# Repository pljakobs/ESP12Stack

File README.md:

# ESP12Stack
### An ESP12 Platform, adhering to the 30x30mm breakout boards often found but much more functional.
I have tested it with:
- ESPEasy
- SONOFF-TASMOTA
- Micropython
- Arduino
### Hardware
At this point, there is the base board which has:
- an ESP12 with all GPIO Pins brought to 2.54mm pin headers along the edge
- four WS2812B RGB or SK6812 RGBW individually addressable LEDs, which can be configured to be driven by various GPIO pins using 470Ohm resistors:
  - J02 -> GPIO2
  - J04 -> GPIO4
  - J05 -> GPIO5
  - J12 -> GPIO12
  - J13 -> GPIO13
only one of those should be installed at any given time
- low drop 3.3V regulator, the system can be powered either via the on-board USB connector or the 5V Vcc pin. Since there's no protection and those two 5V supplies form just one net, I suggest never to use both at the same time to avoid damage to your USB power source
- miniature switches for GPIO0 (FLASH) and RESET
- all necessary pull up / pull down resistors to be working as a stand alone device

In the FTDI vesion (currently untested) I have added an FTDI232 chip which should make the whole device in-place programmable, so no external USB-UART adapter is needed. Just plug it in to your PCs USB and you can talk to the ESP's UART
### There are a few other boards as well
- a 12-36V Switching Power Supply board that provides 5V (provided the feedback resistors are set correctly) to power the stack in an environment that requires those power levels (like a car)
- a five channel MOSFET board that can drive common anode LED strips
- an "experimentation" board that only has the VCC and GND pins pulled out to the outer row of mounting holes and otherwise offers as much of a "standard" layout board as possible for your own devices
### What I'm, working on:
the next board to come should be a display that just plugs on top of the base board, offering 240x240px through I2C

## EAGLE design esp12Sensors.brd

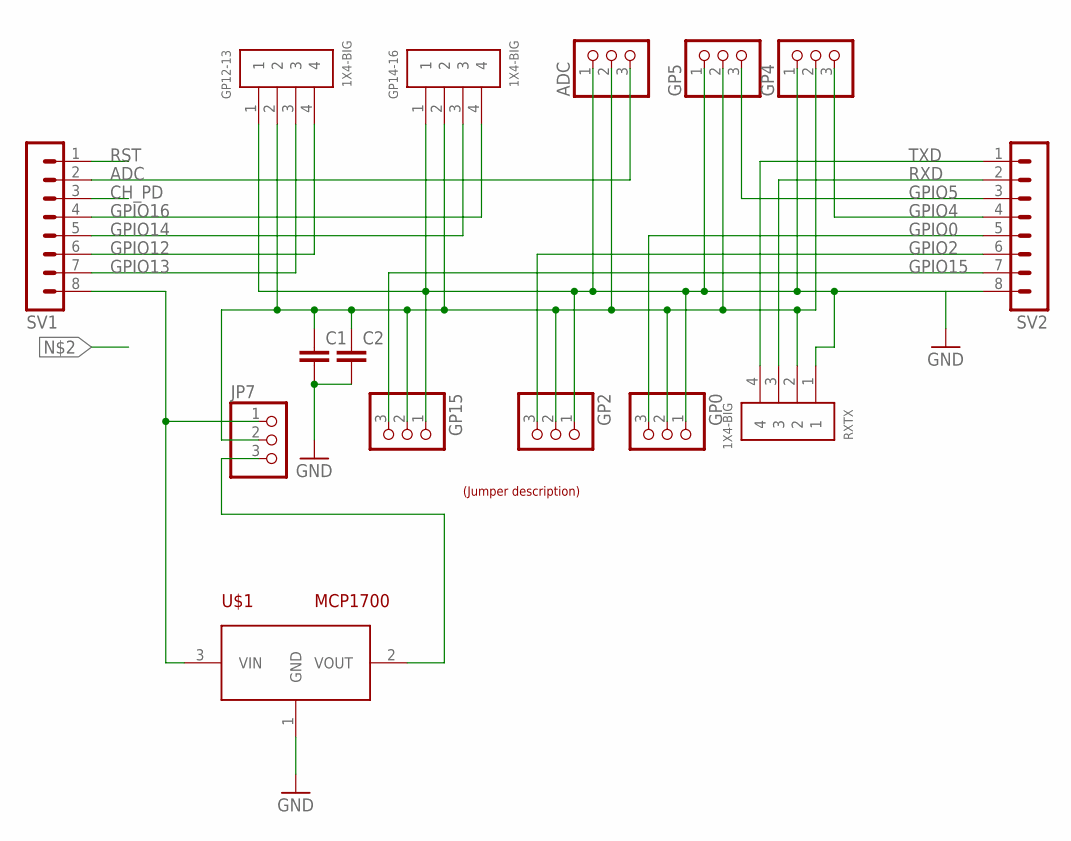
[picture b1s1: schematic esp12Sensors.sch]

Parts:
ADC: PINHD-1X3; 1X03
C1, C2: C-EUC0805; C0805
GP0, GP2, GP4, GP5, GP15: PINHD-1X3; 1X03
GP12-13, GP14-16: 1X4-BIG; 1X04-BIG
JP7: PINHD-1X3; 1X03
RXTX: 1X4-BIG; 1X04-BIG
SV1, SV2: MA08-1
U$1: MCP1700; SOT-23
U$2: LABEL_JUMPER_1X3; JUMP3_DESC

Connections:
3V3: JP7.3, U$1.2 (VOUT)
ADC: ADC.3, SV1.2
CH_PD: SV1.3
GND: ADC.1, C1.2, C2.2, GP0.1, GP2.1, GP4.1, GP5.1, GP12-13.1, GP14-16.1, GP15.1, RXTX.1, SV2.8, U$1.1 (GND)
GP12-13: JP7.1, SV1.8, U$1.3 (VIN)
GPIO0: GP0.3, SV2.5
GPIO2: GP2.3, SV2.6
GPIO4: GP4.3, SV2.4
GPIO5: GP5.3, SV2.3
GPIO12: GP12-13.3, SV1.7
GPIO13: GP12-13.4, SV1.6
GPIO14: GP14-16.3, SV1.5
GPIO15: GP15.3, SV2.7
GPIO16: GP14-16.4, SV1.4
RST: SV1.1
RXD: RXTX.3, SV2.2
TXD: RXTX.4, SV2.1
VCC: ADC.2, C1.1, C2.1, GP0.2, GP2.2, GP4.2, GP5.2, GP12-13.2, GP14-16.2, GP15.2, JP7.2, RXTX.2

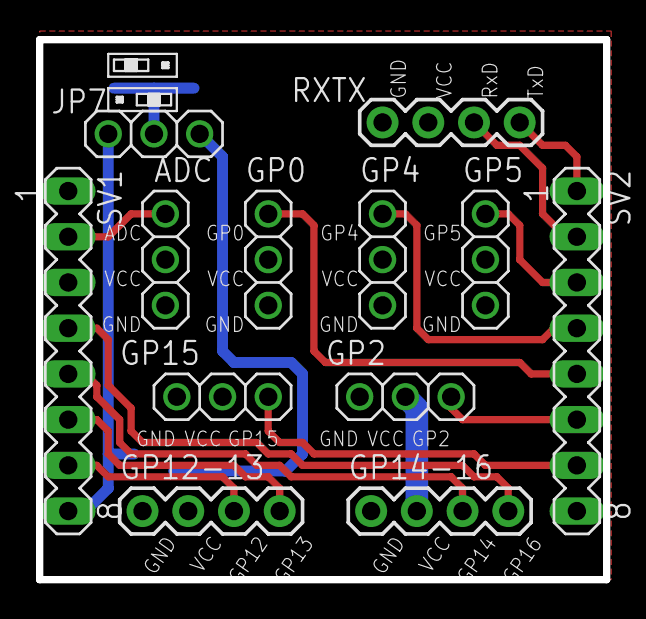
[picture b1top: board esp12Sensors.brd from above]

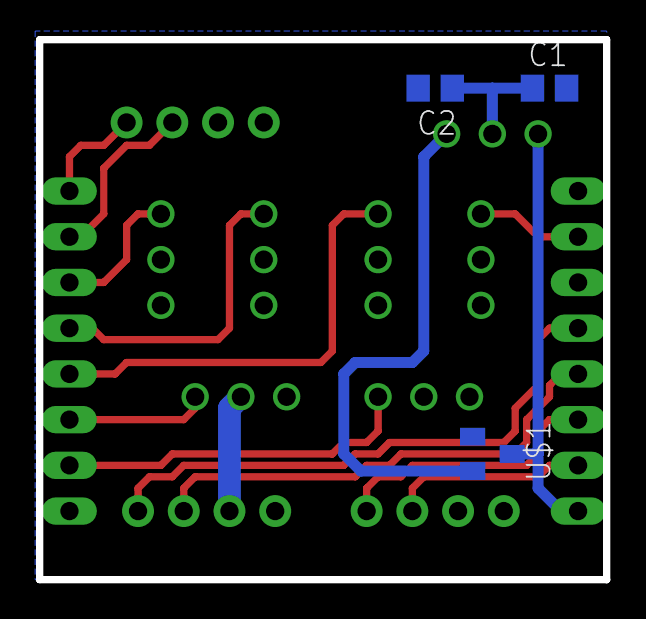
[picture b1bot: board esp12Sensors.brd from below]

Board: 2 copper layers, 31.5 x 30.0 mm, 16 parts (3 on the bottom side), 16 nets.

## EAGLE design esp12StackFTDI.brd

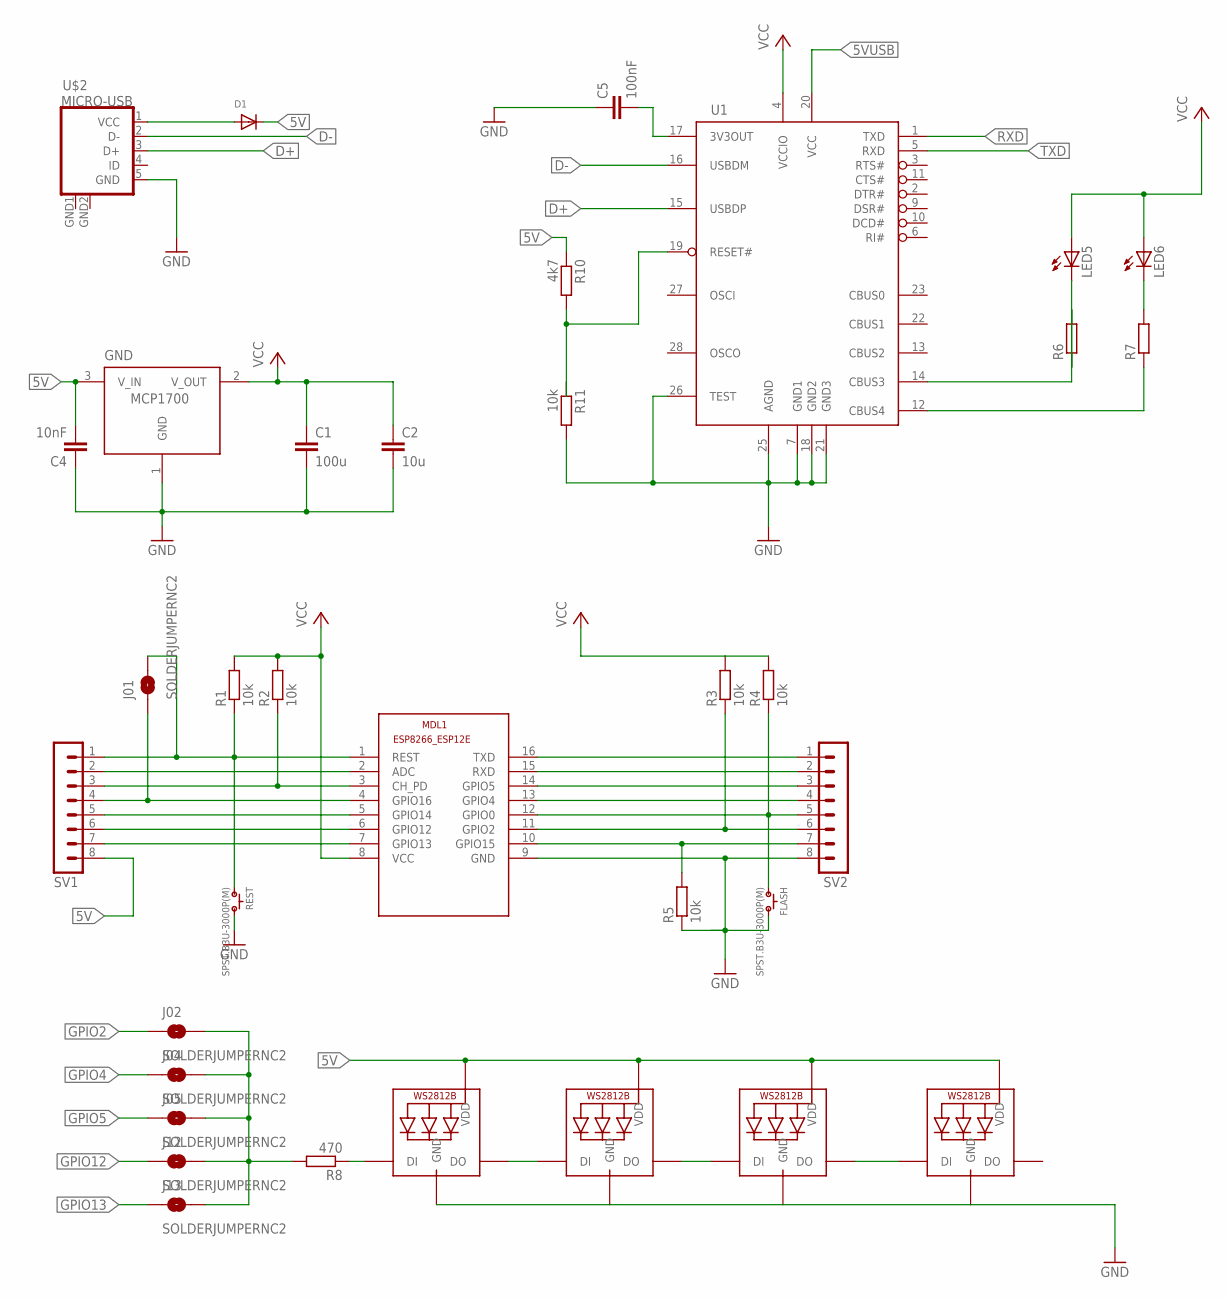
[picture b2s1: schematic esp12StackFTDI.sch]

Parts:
C1: 100u; C0805
C2: 10u; C0805
C4: 10nF; C0805
C5: 100nF; C0805
D1: DIODESOD-323F; SOD-323F
FLASH: SPST.B3U-3000P(M); B3U-3000P(M)
GND: MCP1700SOT23; SOT-23
J01, J02, J04, J05, J12, J13: SOLDERJUMPERNC2; SJ_2S-NOTRACE
LED1, LED2, LED3, LED4: WS2812B5050; WS2812B
LED5, LED6: LEDCHIPLED_0603; CHIPLED_0603
MDL1: ESP8266-12EESP8266-ESP12E; ESP8266-ESP12E
R1, R2, R3, R4, R5, R11: 10k; R0603
R6, R7: R-EU_R0603; R0603
R8: 470; R0603
R10: 4k7; R0603
REST: SPST.B3U-3000P(M); B3U-3000P(M)
SV1, SV2: MA08-1
U1: FT232RL; SSOP28DB
U$2: MICRO-USB

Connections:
3V3: C1.1, C2.1, GND.2 (V_OUT), LED5.A, LED6.A, MDL1.8 (VCC), R1.2, R2.2, R3.2, R4.2, U1.4 (VCCIO)
3V3OUT: C5.2, U1.17 (3V3OUT)
5V: C4.2, D1.C, GND.3 (V_IN), LED1.1-VDD (VDD), LED2.1-VDD (VDD), LED3.1-VDD (VDD), LED4.1-VDD (VDD), R10.1, SV1.8, U1.20 (VCC)
5VUSB: D1.A, U$2.1 (VCC)
ADC: MDL1.2 (ADC), SV1.2
CBUS3: R6.2, U1.14 (CBUS3)
CBUS4: R7.1, U1.12 (CBUS4)
CH_PD: MDL1.3 (CH_PD), R2.1, SV1.3
D+: U1.15 (USBDP), U$2.3 (D+)
D-: U1.16 (USBDM), U$2.2 (D-)
DIN1: J02.2, J04.2, J05.2, J12.2, J13.2, R8.2
DOUT1DIN2: LED1.2-DOUT (DO), LED2.4-DIN (DI)
DOUT2DIN3: LED2.2-DOUT (DO), LED3.4-DIN (DI)
DOUT3DIN4: LED3.2-DOUT (DO), LED4.4-DIN (DI)
GND: C1.2, C2.2, C4.1, C5.1, FLASH.2, GND.1 (GND), LED1.3-GND (GND), LED2.3-GND (GND), LED3.3-GND (GND), LED4.3-GND (GND), MDL1.9 (GND), R5.1, R11.2, REST.2, SV2.8, U1.7 (GND1), U1.18 (GND2), U1.21 (GND3), U1.25 (AGND), U1.26 (TEST), U$2.5 (GND), U$2.GND1 (GND), U$2.GND2 (GND)
GPIO0: FLASH.1, MDL1.12 (GPIO0), R4.1, SV2.5
GPIO2: J02.1, MDL1.11 (GPIO2), R3.1, SV2.6
GPIO4: J04.1, MDL1.13 (GPIO4), SV2.4
GPIO5: J05.1, MDL1.14 (GPIO5), SV2.3
GPIO12: J12.1, MDL1.6 (GPIO12), SV1.6
GPIO13: J13.1, MDL1.7 (GPIO13), SV1.7
GPIO14: MDL1.5 (GPIO14), SV1.5
GPIO15: MDL1.10 (GPIO15), R5.2, SV2.7
GPIO16: J01.1, MDL1.4 (GPIO16), SV1.4
LED_RX: LED6.C, R7.2
LED_TX: LED5.C, R6.1
unnamed: LED1.4-DIN (DI), R8.1
RESET: R10.2, R11.1, U1.19 (RESET#)
REST: J01.2, MDL1.1 (REST), R1.1, REST.1, SV1.1
RXD: MDL1.15 (RXD), SV2.2, U1.1 (TXD)
TXD: MDL1.16 (TXD), SV2.1, U1.5 (RXD)

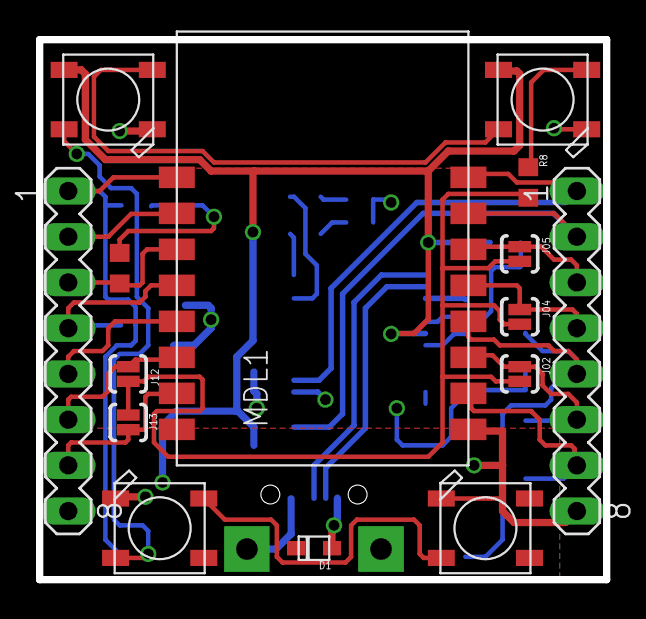
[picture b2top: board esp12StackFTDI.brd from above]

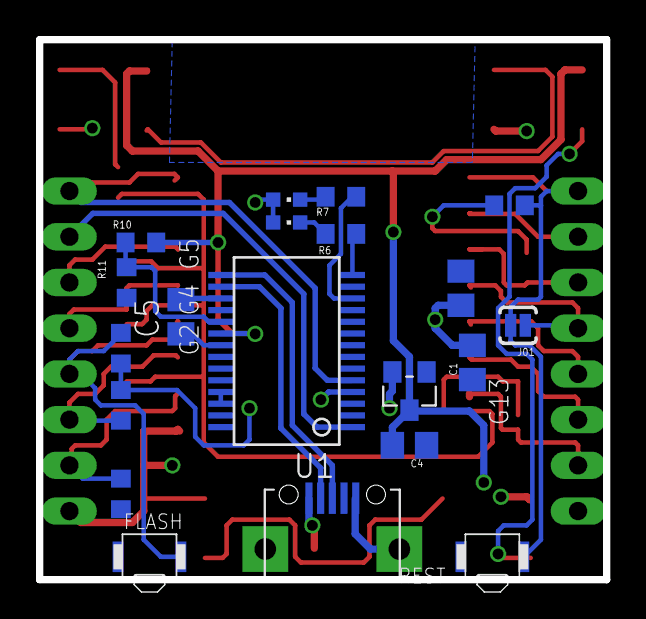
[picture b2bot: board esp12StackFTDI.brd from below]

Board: 2 copper layers, 31.5 x 30.0 mm, 35 parts (20 on the bottom side), 31 nets.

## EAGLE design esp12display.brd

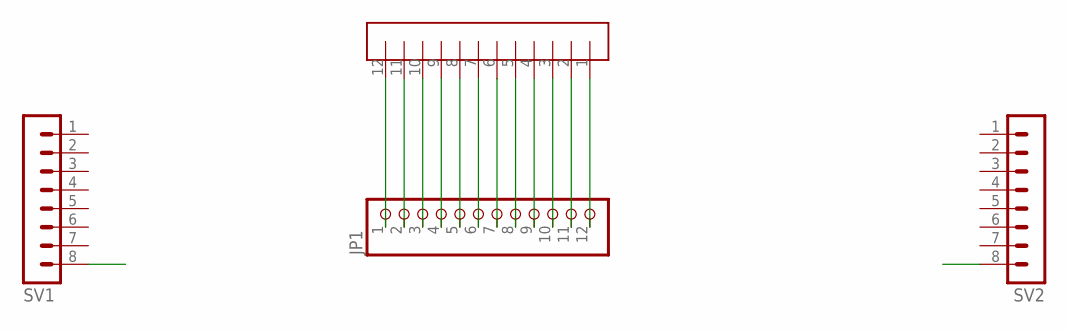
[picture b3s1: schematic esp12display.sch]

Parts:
JP1: PINHD-1X12; 1X12
SV1, SV2: MA08-1
U$1: 12PIN_LCD_PADS; PINS_ONLY

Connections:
GND: SV2.8
unnamed: JP1.1, U$1.12
unnamed: JP1.2, U$1.11
unnamed: JP1.3, U$1.10
unnamed: JP1.4, U$1.9
unnamed: JP1.5, U$1.8
unnamed: JP1.6, U$1.7
unnamed: JP1.7, U$1.6
unnamed: JP1.8, U$1.5
unnamed: JP1.9, U$1.4
unnamed: JP1.10, U$1.3
unnamed: JP1.11, U$1.2
unnamed: JP1.12, U$1.1

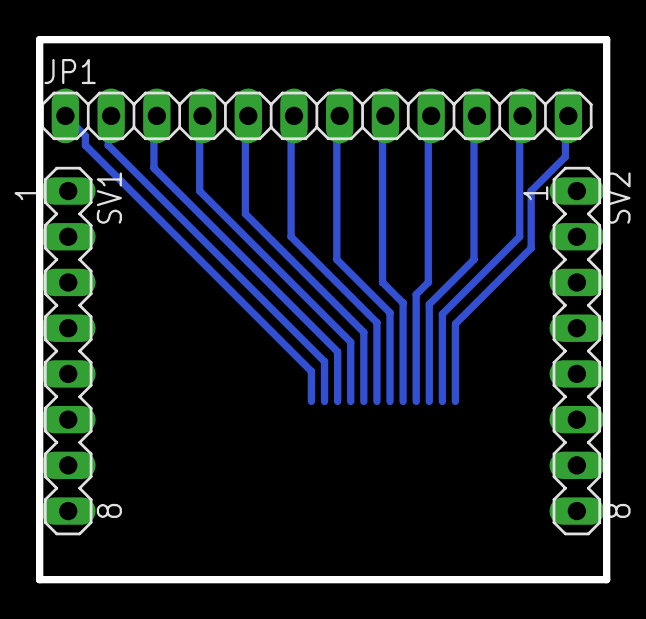
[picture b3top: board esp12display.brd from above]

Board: 2 copper layers, 31.5 x 30.0 mm, 4 parts (1 on the bottom side), 12 nets.

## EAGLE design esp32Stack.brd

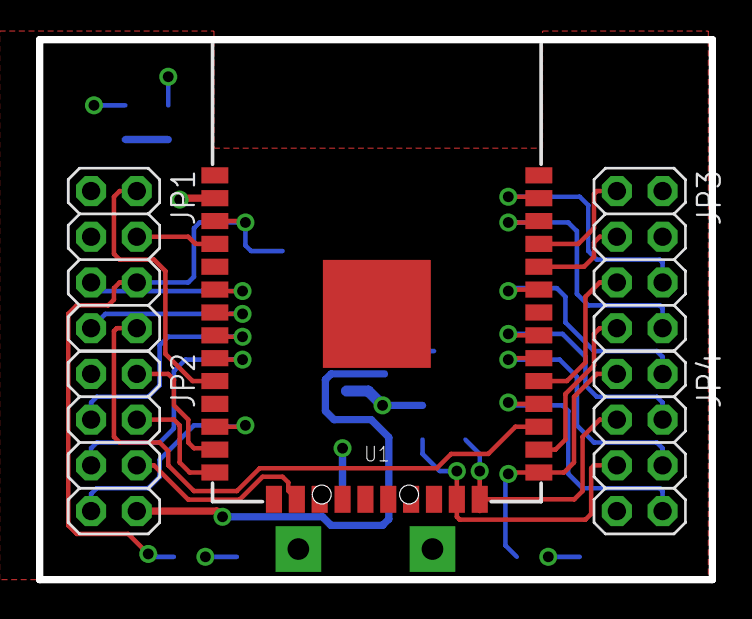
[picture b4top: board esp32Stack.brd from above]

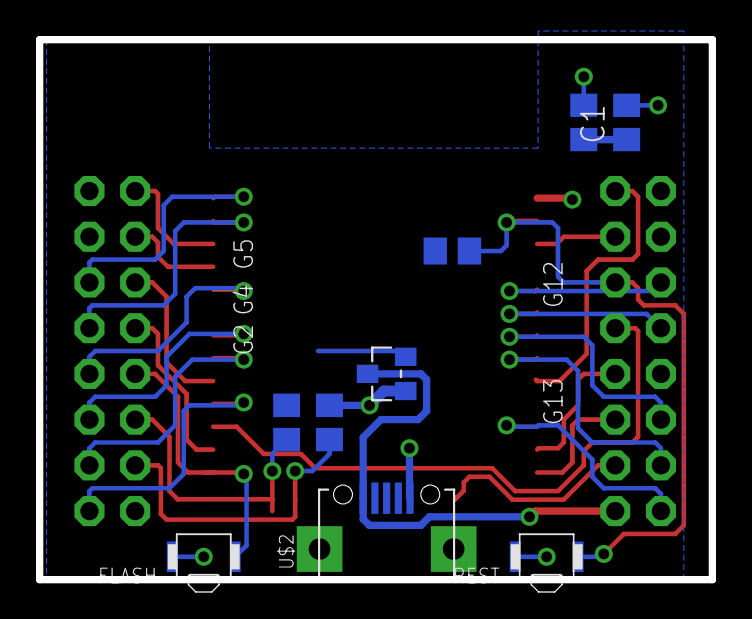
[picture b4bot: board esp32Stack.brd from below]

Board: 2 copper layers, 37.4 x 30.0 mm, 14 parts (9 on the bottom side), 28 nets.

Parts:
C1: 100u; C0805
C2: 10u; C0805
FLASH: SPST.B3U-3000P(M); B3U-3000P(M)
GND: MCP1700SOT23; SOT-23
JP1, JP2, JP3, JP4: 2X04
R2, R3, R5: 10k; R0805
REST: SPST.B3U-3000P(M); B3U-3000P(M)
U1: ESP-WROOM-03
U$2: MICRO-USB

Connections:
3V3: C1.1, C2.1, GND.2, R2.2, R3.2, U1.2
+5V: GND.3, JP2.8, U$2.1
ADC: JP1.4, U1.4
EN: JP1.6, R2.1, REST.1, U1.3
GND: C1.2, C2.2, FLASH.2, GND.1, JP4.7, R5.1, REST.2, U1.1, U1.5, U1.15, U1.38, U1.GND, U$2.5, U$2.GND1, U$2.GND2
GPIO0: FLASH.1, JP4.1, U1.25
GPIO2: JP4.3, R3.1, U1.24
GPIO4: JP3.7, U1.26
GPIO5: JP3.5, U1.29
GPIO12: JP2.4, U1.14
GPIO13: JP2.6, U1.16
GPIO14: JP2.2, U1.13
GPIO15: JP4.5, R5.2, U1.23
GPIO16: JP1.8, U1.27
GPIO17: JP4.8, U1.28
GPIO18: JP4.6, U1.30
GPIO19: JP4.4, U1.31
GPIO21: JP4.2, U1.33
GPIO22: JP3.8, U1.36
GPIO23: JP3.6, U1.37
GPIO25: JP1.2, U1.10
GPIO27: JP2.7, U1.12
GPIO32: JP2.3, U1.8
GPIO33: JP2.5, U1.9
GPIO34: JP1.5, U1.6
GPIO35: JP1.7, U1.7
RXD: JP3.3, U1.34
TXD: JP3.1, U1.35

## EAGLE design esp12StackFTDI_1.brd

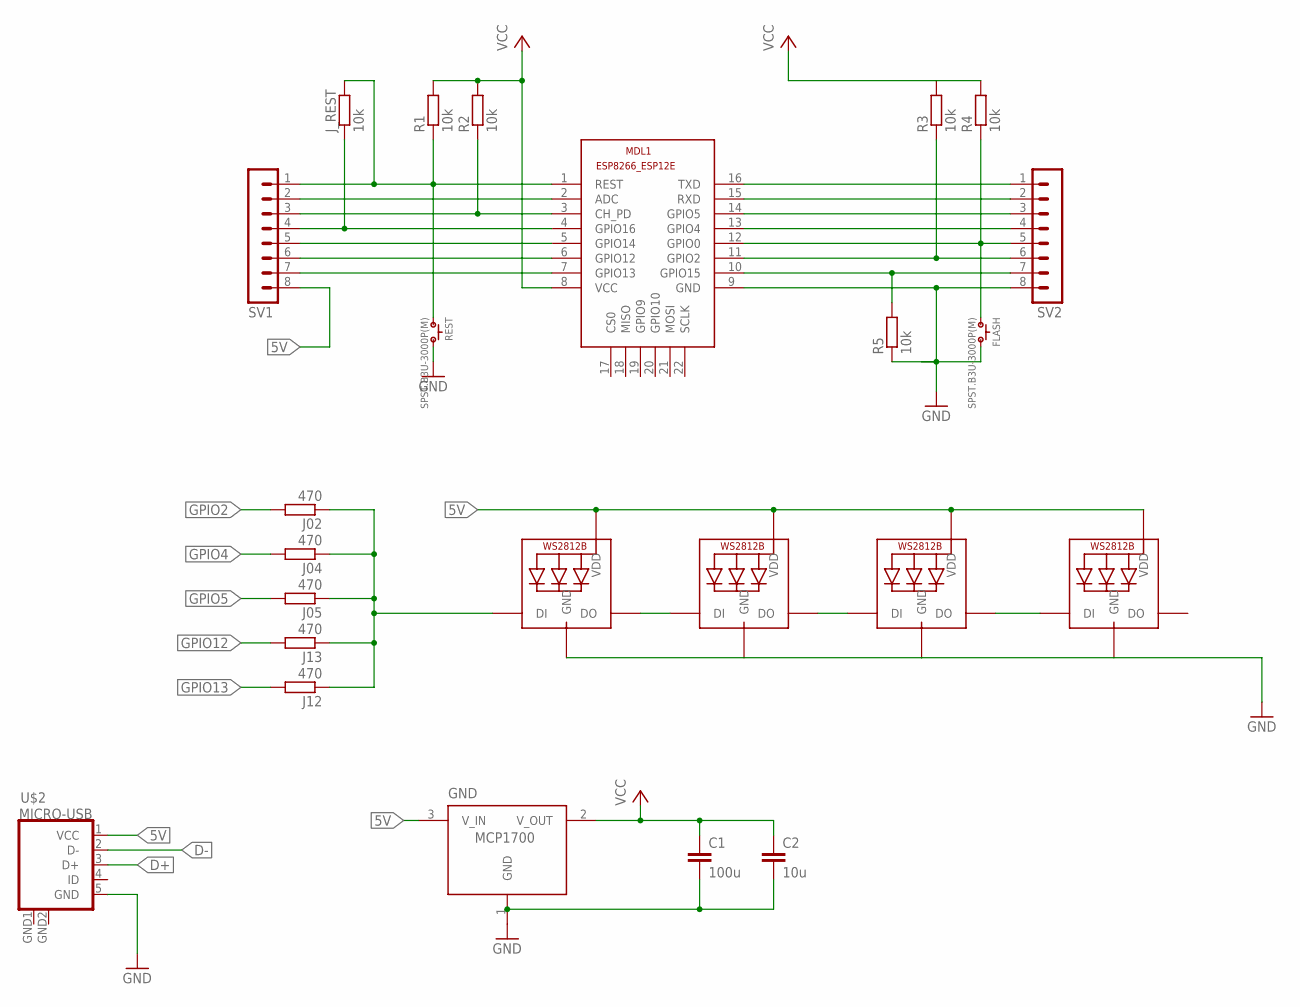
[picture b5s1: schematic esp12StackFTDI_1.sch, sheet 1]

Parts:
C1: 100u; C0805
C2: 10u; C0805
FLASH: SPST.B3U-3000P(M); B3U-3000P(M)
GND: MCP1700SOT23; SOT-23
J02, J04, J05, J12, J13: 470; R0603
J_REST: 10k; R0603
LED1, LED2, LED3, LED4: WS2812B5050; WS2812B
MDL1: ESP8266-12EESP8266-ESP12E; ESP8266-ESP12E
R1, R2, R3, R4, R5: 10k; R0603
REST: SPST.B3U-3000P(M); B3U-3000P(M)
SV1, SV2: MA08-1
U$2: MICRO-USB

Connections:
3V3: C1.1, C2.1, GND.2 (V_OUT), MDL1.8 (VCC), R1.2, R2.2, R3.2, R4.2; also elsewhere on the board
5V: GND.3 (V_IN), LED1.1-VDD (VDD), LED2.1-VDD (VDD), LED3.1-VDD (VDD), LED4.1-VDD (VDD), SV1.8, U$2.1 (VCC); also elsewhere on the board
ADC: MDL1.2 (ADC), SV1.2
CH_PD: MDL1.3 (CH_PD), R2.1, SV1.3
D+: U$2.3 (D+); also elsewhere on the board
D-: U$2.2 (D-); also elsewhere on the board
DIN1: J02.1, J04.1, J05.1, J12.1, J13.1, LED1.4-DIN (DI)
DOUT1DIN2: LED1.2-DOUT (DO), LED2.4-DIN (DI)
DOUT2DIN3: LED2.2-DOUT (DO), LED3.4-DIN (DI)
DOUT3DIN4: LED3.2-DOUT (DO), LED4.4-DIN (DI)
GND: C1.2, C2.2, FLASH.2, GND.1 (GND), LED1.3-GND (GND), LED2.3-GND (GND), LED3.3-GND (GND), LED4.3-GND (GND), MDL1.9 (GND), R5.1, REST.2, SV2.8, U$2.5 (GND), U$2.GND1 (GND), U$2.GND2 (GND); also elsewhere on the board
GPIO0: FLASH.1, MDL1.12 (GPIO0), R4.1, SV2.5
GPIO2: J02.2, MDL1.11 (GPIO2), R3.1, SV2.6
GPIO4: J04.2, MDL1.13 (GPIO4), SV2.4
GPIO5: J05.2, MDL1.14 (GPIO5), SV2.3
GPIO12: J13.2, MDL1.6 (GPIO12), SV1.6
GPIO13: J12.2, MDL1.7 (GPIO13), SV1.7
GPIO14: MDL1.5 (GPIO14), SV1.5
GPIO15: MDL1.10 (GPIO15), R5.2, SV2.7
GPIO16: J_REST.1, MDL1.4 (GPIO16), SV1.4
REST: J_REST.2, MDL1.1 (REST), R1.1, REST.1, SV1.1
RXD: MDL1.15 (RXD), SV2.2; also elsewhere on the board
TXD: MDL1.16 (TXD), SV2.1; also elsewhere on the board

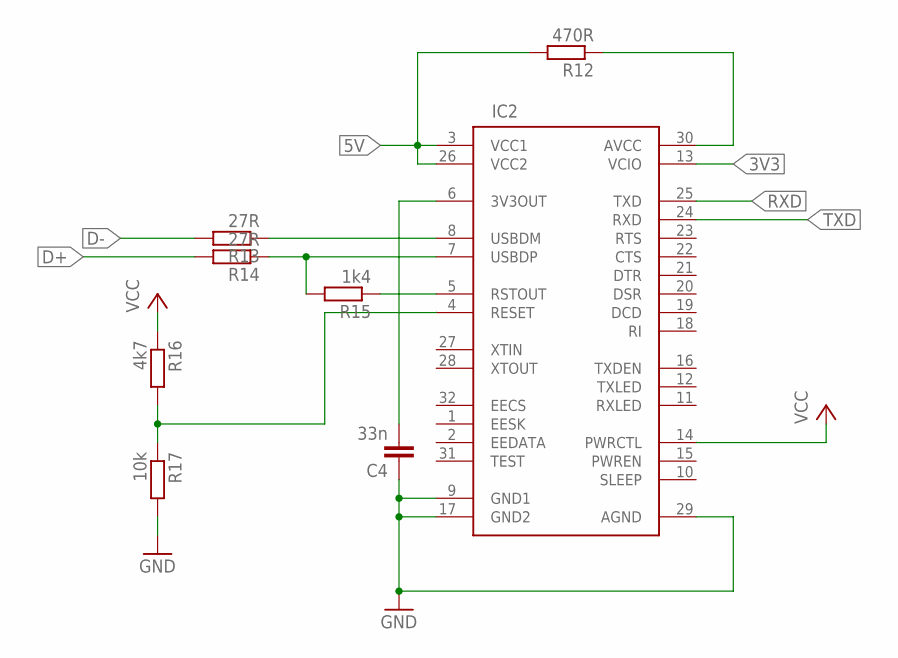
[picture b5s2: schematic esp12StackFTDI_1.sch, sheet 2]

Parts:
C4: 33n; C0603
IC2: FT232BM; QFP-32
R12: 470R; R0603
R13, R14: 27R; R0603
R15: 1k4; R0603
R16: 4k7; R0603
R17: 10k; R0603

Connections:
3V3: IC2.13 (VCIO), IC2.14 (PWRCTL); also elsewhere on the board
3V3OUT1: C4.2, IC2.6 (3V3OUT)
5V: IC2.3 (VCC1), IC2.26 (VCC2), R12.2, R16.1; also elsewhere on the board
AVCC1: IC2.30 (AVCC), R12.1
D+: R14.2; also elsewhere on the board
D-: R13.2; also elsewhere on the board
GND: C4.1, IC2.9 (GND1), IC2.17 (GND2), IC2.29 (AGND), R17.2; also elsewhere on the board
RESET1: IC2.4 (RESET), R16.2, R17.1
RSTOUT1: IC2.5 (RSTOUT), R15.1
RXD: IC2.25 (TXD); also elsewhere on the board
TXD: IC2.24 (RXD); also elsewhere on the board
USBDM1: IC2.8 (USBDM), R13.1
USBDP1: IC2.7 (USBDP), R14.1, R15.2

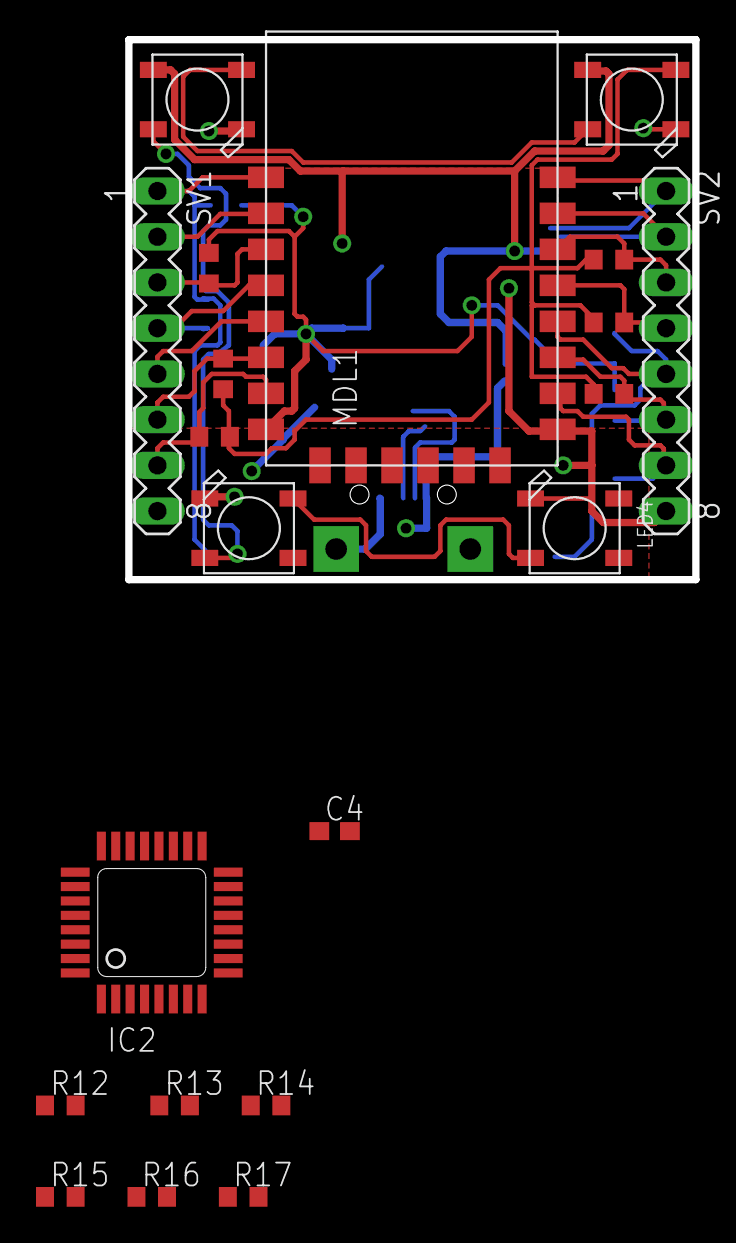
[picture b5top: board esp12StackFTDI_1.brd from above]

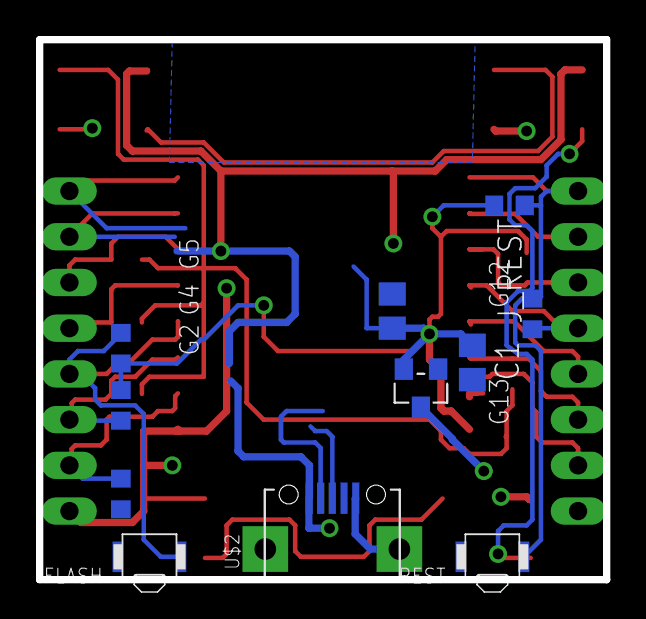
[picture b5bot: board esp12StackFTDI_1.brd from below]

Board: 2 copper layers, 31.5 x 30.0 mm, 32 parts (11 on the bottom side), 29 nets.

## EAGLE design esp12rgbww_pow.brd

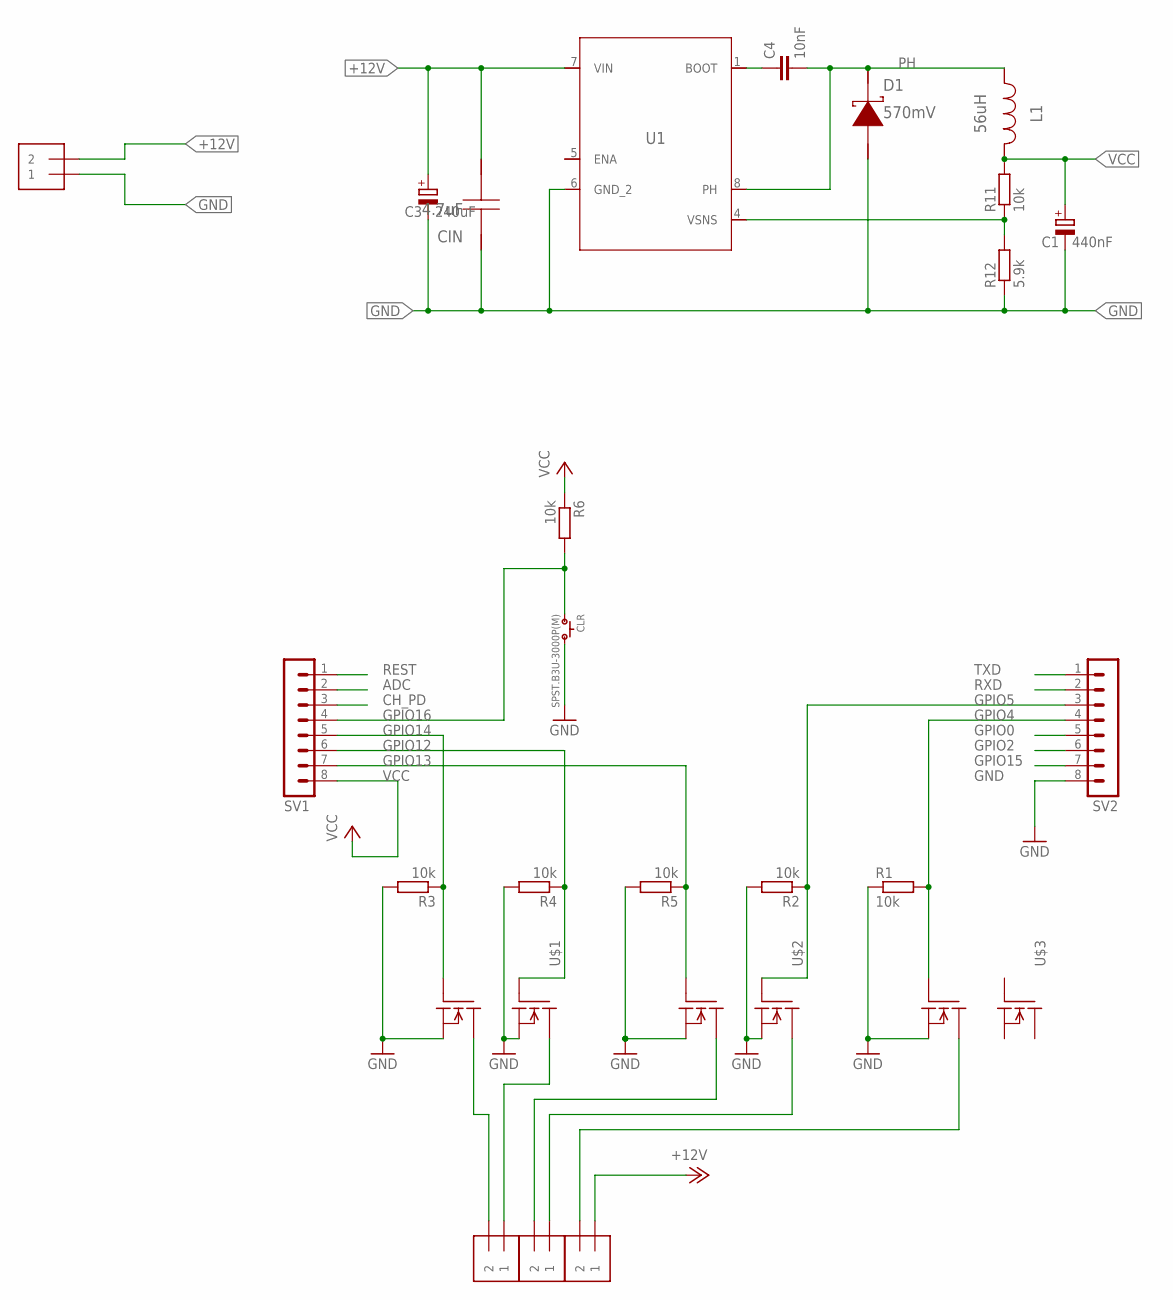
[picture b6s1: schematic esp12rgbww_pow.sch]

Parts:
C1: 440nF; E2,5-7
C3: 240uF; E2,5-7
C4: 10nF; C0805
CIN: 4.7uF; 1206
CLR: SPST.B3U-3000P(M); B3U-3000P(M)
D1: 570mV; SMA
J1, J2, J3, J4: 1X2-3.5MM
L1: 56uH; IND_NPI75C
R1, R2, R3, R4, R5, R6, R11: 10k; R0805
R12: 5.9k; R0805
SV1, SV2: MA08-1
U1: TPS5410DR; M08A
U$1, U$2, U$3: AOD4806; SO08

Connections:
+12V: C3.+, CIN.2, J3.1, J4.2, U1.7 (VIN)
ADC: SV1.2
B: J1.2, U$1.7 (D1), U$1.8 (D1)
BOOT: C4.1, U1.1 (BOOT)
CH_PD: SV1.3
CW: J2.1, U$2.5 (D), U$2.6 (D)
G: J1.1, U$1.5 (D), U$1.6 (D)
GND: C1.-, C3.-, CIN.1, CLR.2, D1.2 (A), J4.1, R1.1, R2.2, R3.2, R4.2, R5.2, R12.1, SV2.8, U1.6 (GND_2), U$1.1 (S1), U$1.3 (S), U$2.1 (S1), U$2.3 (S), U$3.1 (S1)
GPIO0: SV2.5
GPIO2: SV2.6
GPIO4: R1.2, SV2.4, U$3.2 (G1)
GPIO5: R2.1, SV2.3, U$2.4 (G)
GPIO12: R4.1, SV1.6, U$1.4 (G)
GPIO13: R5.1, SV1.7, U$2.2 (G1)
GPIO14: R3.1, SV1.5, U$1.2 (G1)
GPIO15: SV2.7
GPIO16: CLR.1, R6.2, SV1.4
PH: C4.2, D1.1 (K), L1.2, U1.8 (PH)
R: J2.2, U$2.7 (D1), U$2.8 (D1)
REST: SV1.1
RXD: SV2.2
SENS: R11.1, R12.2, U1.4 (VSNS)
TXD: SV2.1
VCC: C1.+, L1.1, R6.1, R11.2, SV1.8
WW: J3.2, U$3.7 (D1), U$3.8 (D1)

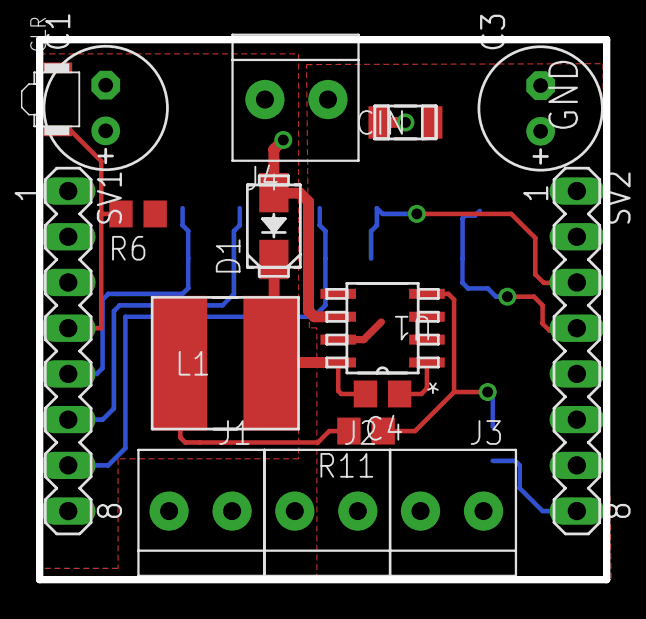
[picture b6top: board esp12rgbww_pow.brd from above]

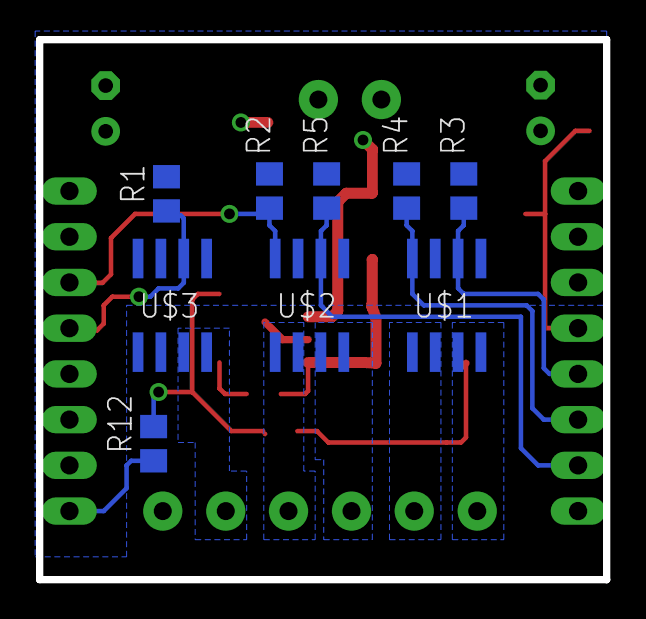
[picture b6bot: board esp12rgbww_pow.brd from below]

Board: 2 copper layers, 31.5 x 30.0 mm, 25 parts (9 on the bottom side), 17 nets.

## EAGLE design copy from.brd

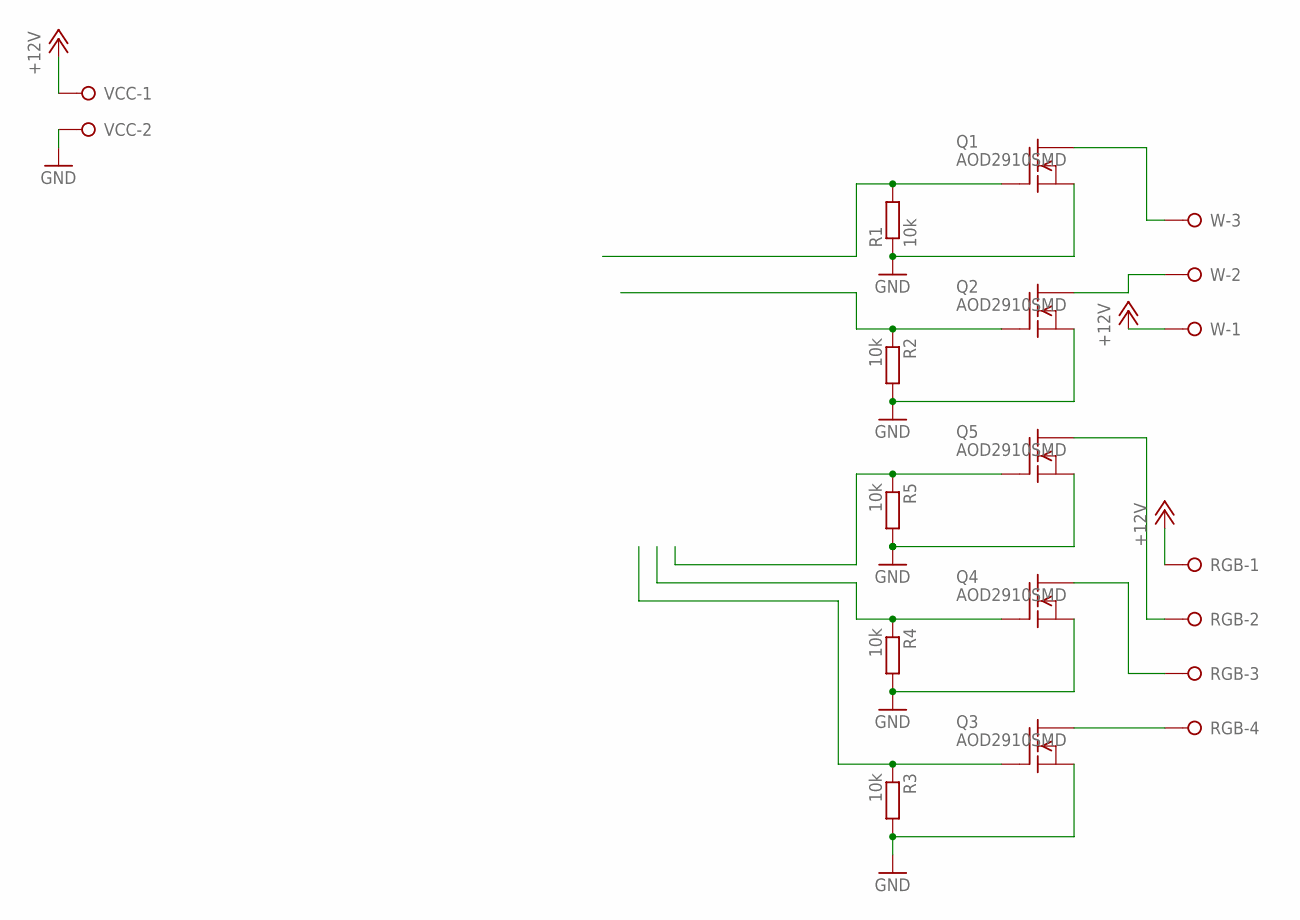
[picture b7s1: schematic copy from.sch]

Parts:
Q1, Q2, Q3, Q4, Q5: AOD2910SMD; DPAK-3
R1, R2, R3, R4, R5: 10k; R0805
RGB: W237-04P; W237-4P
VCC: W237-02P; W237-132
W: W237-03P; W237-133

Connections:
+12V: RGB.1, VCC.1, W.1
B: Q3.4 (D), RGB.4
CW: Q2.4 (D), W.2
G: Q4.4 (D), RGB.3
GND: Q1.3 (S), Q2.3 (S), Q3.3 (S), Q4.3 (S), Q5.3 (S), R1.1, R2.2, R3.2, R4.2, R5.2, VCC.2
R: Q5.4 (D), RGB.2
RGB-B: Q3.1 (G), R3.1
RGB-CW: Q2.1 (G), R2.1
RGB-G: Q4.1 (G), R4.1
RGB-R: Q5.1 (G), R5.1
RGB-WW: Q1.1 (G), R1.2
WW: Q1.4 (D), W.3

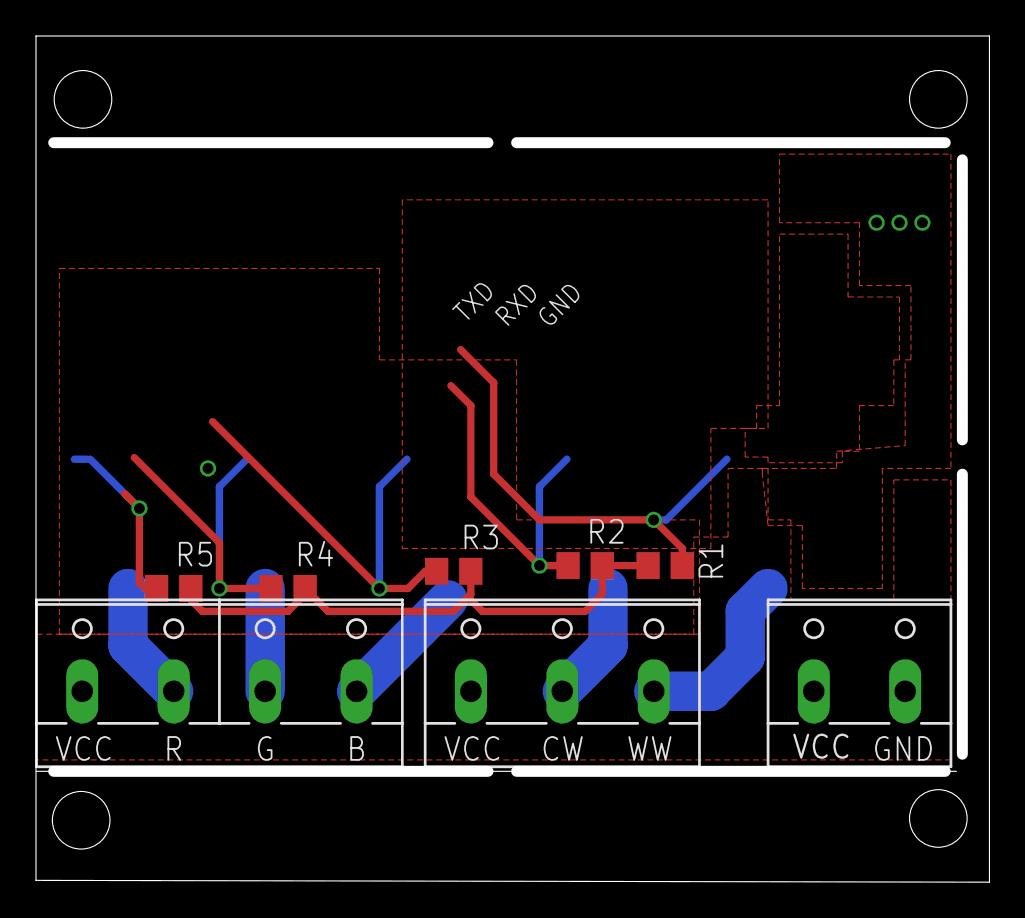
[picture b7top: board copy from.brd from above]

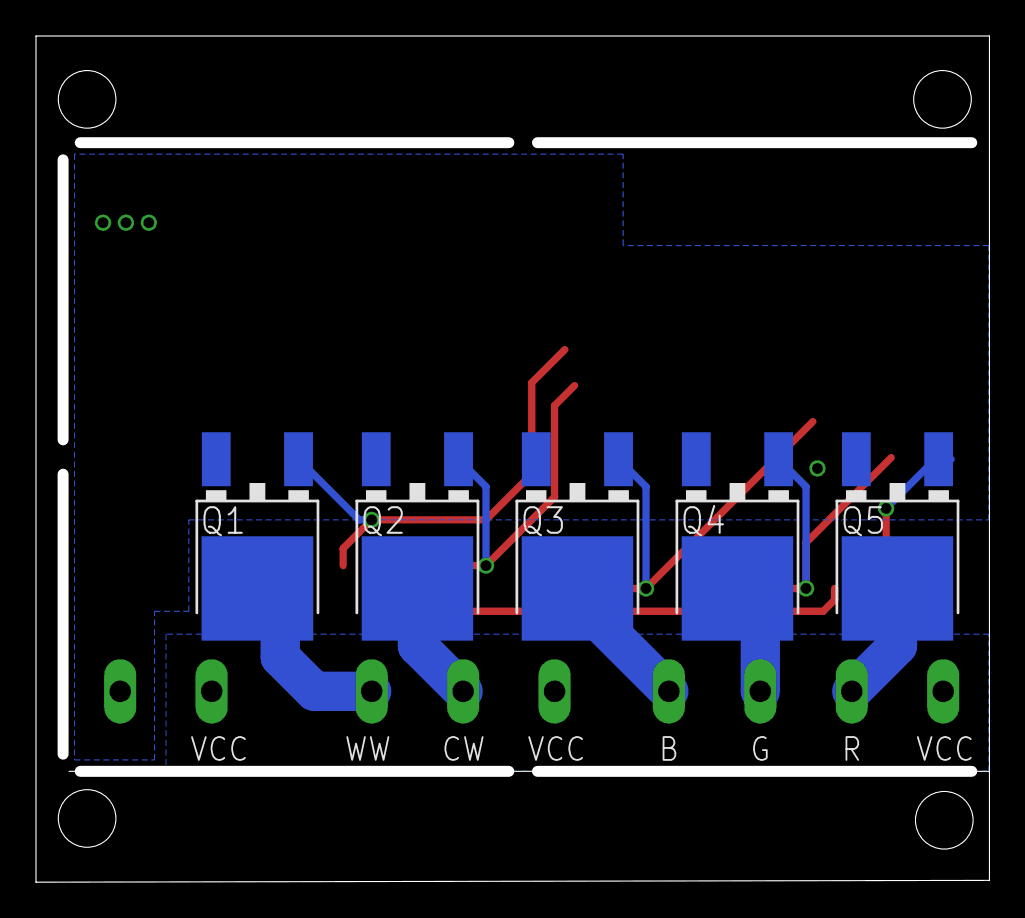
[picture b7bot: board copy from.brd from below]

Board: 2 copper layers, 52.4 x 46.4 mm, 13 parts (5 on the bottom side), 12 nets.

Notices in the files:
parts and their libraries:
SparkFun: Licensing: CC v3.0 Share-Alike You are welcome to use this library for commercial purposes.
FTDI: FTDI USB-serial converters and FIFOs, © UNITRONIC AG
